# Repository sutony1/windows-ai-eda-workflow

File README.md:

# Windows AI EDA Workflow

图文案例现已发布：[从 SPICE 仿真到 KiCad 10 PCB](https://sutony1.github.io/windows-ai-eda-workflow/)。

一套在 Windows 10/11 上可复现的 AI 辅助电子设计流程：

`SPICE 仿真 -> KiCad 10 原理图/PCB -> ERC/DRC -> Gerber -> 嘉立创报价/生产`

它保存流程、脚本、Codex Skill 和一个已验证示例，不复制第三方软件或厂商宏模型。

## 已验证基线

| 工具 | 本机已验证版本 |
|---|---|
| KiCad | 10.0.5 x64 |
| mixelpixx KiCAD-MCP-Server | 2.6.0，commit `0dc3ee8` |
| ngspice | 本机 42+ Windows x64/KLU；新装推荐官方稳定版 46 |
| LTspice | 26.0.2.1 |
| 嘉立创 EDA 专业版 | 3.2.175 |
| easyeda-agent | 已验证 0.21.2；上游最新 0.21.4；CLI、连接器、Skill 必须同版 |
| Node.js | 24.13.1（MCP 至少建议 Node 20） |

## 新电脑最快复现

```powershell
git clone https://github.com/sutony1/windows-ai-eda-workflow.git
cd windows-ai-eda-workflow
powershell -ExecutionPolicy Bypass -File .\install.ps1
powershell -ExecutionPolicy Bypass -File .\skills\windows-ai-eda-workflow\scripts\Test-AiEdaEnvironment.ps1
```

然后按 [Windows 安装说明](docs/windows-setup.md) 安装工具并重启 Codex。

旧版压缩包迁移说明中的原句也继续适用：**解压到其他机器的 `%USERPROFILE%\.codex\skills\` 后，按新文档安装 ngspice 与 KiCad MCP、重启 Codex 即可。** 使用 GitHub 时，推荐运行本仓库的 `install.ps1`，这样旧 Skill 会先被移入可恢复的备份目录。

可以直接把下面这段交给另一台电脑上的 Codex：

```text
请克隆 https://github.com/sutony1/windows-ai-eda-workflow，阅读 README，安装其中三个 Codex Skills，
运行环境检查，并按验证基线配置 KiCad 10、mixelpixx KiCad MCP、ngspice、LTspice、
嘉立创 EDA 专业版和 easyeda-agent。不要替我提交任何生产订单。
```

安装后也可以说：

```text
使用 $windows-ai-eda-workflow 检查这台电脑并恢复 SPICE -> KiCad 10 -> 嘉立创工作流。
```

## 仓库内容

- `skills/windows-ai-eda-workflow/`：跨工具安装、诊断、交付和迁移 Skill。
- `skills/kicad-ct-rms-pcb/`：5 V、0–300 mVrms、50 Hz CT RMS-to-DC 专项 Skill。
- `skills/kicad-ct-simulation/`：此前 KiCad 9/ngspice 阶段的历史 Skill，保留版本陷阱与旧机迁移经验。
- `examples/ct-rms-to-dc/`：KiCad 10 工程、仿真、示波器自动测试和已验证 Gerber。
- `tools/easyeda-conversion-forensics/`：本项目曾用于诊断/修复转换结果的源码；不是标准生产路径。
- `docs/`：安装、设计、EasyEDA/嘉立创和迁移说明。

## 重要边界

KiCad 工程是设计源；EasyEDA 导入件只用于可视化或二次重建。转换后的原理图如果网表为空、元件丢失或 DRC 大量报 `F.Fab` 文字冲突，不能当作正式电气源。裸板下单优先上传由 KiCad 生成并检查过的 Gerber ZIP。

本项目不会自动提交嘉立创订单，不包含 Analog Devices 的 LTC1967 宏模型，也不代替市电安全、绝缘、爬电距离和认证设计。

## 许可证

本仓库自有文档、脚本和示例采用 MIT License。第三方工具、库和厂商模型按各自许可证使用，详见 [THIRD_PARTY.md](THIRD_PARTY.md)。

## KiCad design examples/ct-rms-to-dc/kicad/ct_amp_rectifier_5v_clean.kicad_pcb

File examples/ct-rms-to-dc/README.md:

# 5 V CT RMS-to-DC example

Target: 0–300 mVrms, 50 Hz current-transformer voltage input to approximately 0–3 V DC from a 5 V supply.

## Contents

- `kicad/`: authoritative KiCad 10 schematic, project, and routed PCB.
- `simulation/`: ngspice behavioural smoke test, portable LTspice sweep deck, and measured simulation results.
- `hardware-test/`: PyVISA/RIGOL automated verification example.
- `manufacturing/`: checked Gerber ZIP plus BOM and pick-and-place CSV.

## Selected values

- LTC1967 averaging capacitor: 10 uF.
- OPA2333 gain resistor: 10.0 kOhm, 0.1%.
- Feedback: 93.1 kOhm, 0.1%, plus 5 kOhm multiturn trim; nominal trim about 0.44 kOhm.
- Output filter/isolation: 1 kOhm, 10 uF, and 100 kOhm load.
- Full-scale calibration: adjust 300 mVrms input to 3.000 V output.

The macro-model predicts about 19.5 mV output at zero input after gain. Subtract it in firmware or add a low-offset trim stage if a true zero display is required. Calibrate with the real CT and burden.

## Status

The KiCad board has 126 track segments, zero unconnected pads, and zero error-level DRC findings. A clean-machine CLI run can also report non-electrical silkscreen and library-table warnings; review the full report without confusing those warnings with electrical errors. EasyEDA conversion is not authoritative; use the KiCad source and Gerbers for manufacturing.

## Optional RIGOL automated test

Install a VISA backend and PyVISA, connect the scope over USB or LAN, and list resources before running the script:

```powershell
py -3 -m pip install pyvisa pyvisa-py
py -3 .\hardware-test\rigol_ct_rms_verify.py --help
```

The script does not generate the 50 Hz input by itself; use a calibrated source or supported generator and observe the isolation/grounding rules for the current-transformer test setup.

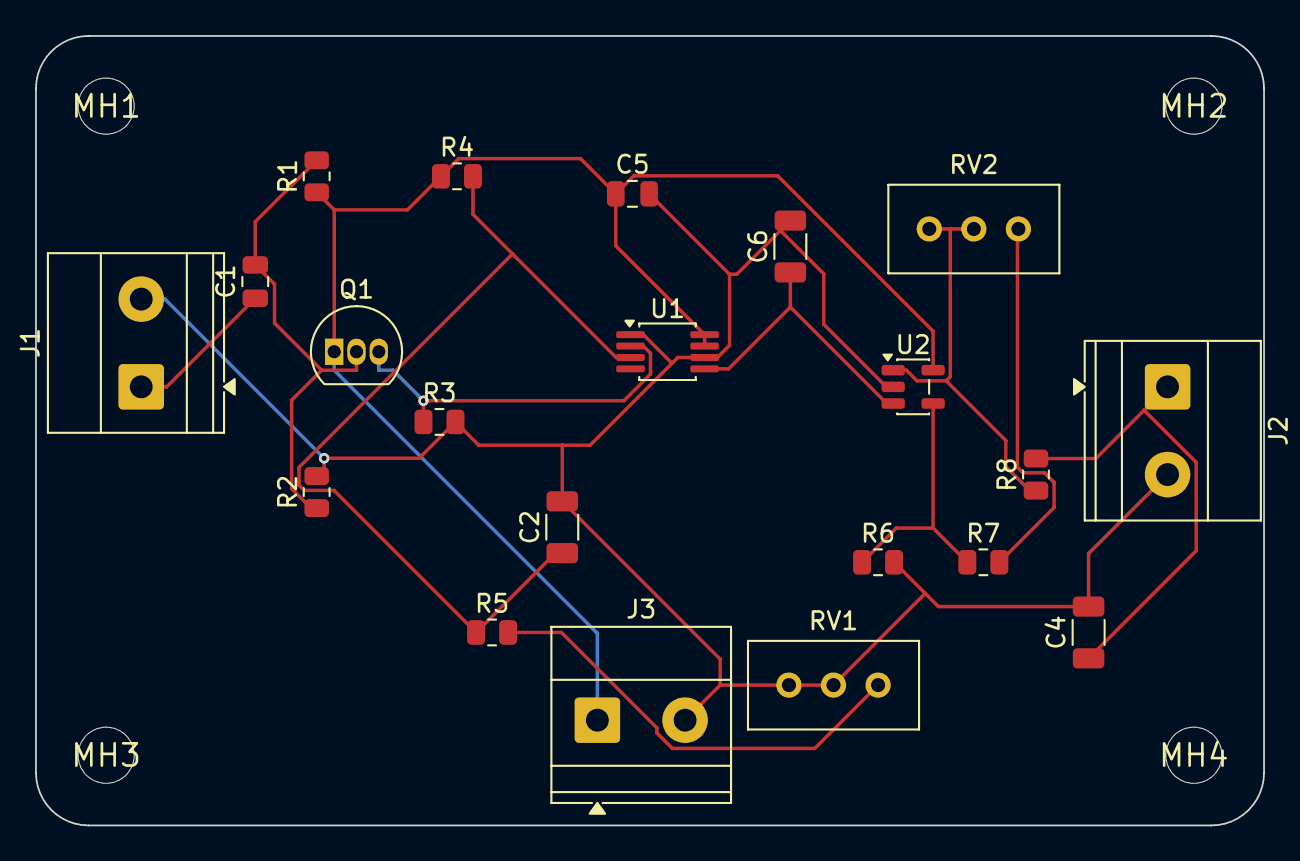
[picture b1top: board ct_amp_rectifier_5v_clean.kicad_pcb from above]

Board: 2 copper layers, 70.0 x 45.0 mm, 25 parts (0 on the bottom side), 12 nets.

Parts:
C1: 1uF; C_0805_2012Metric
C2, C4: 10uF; C_1206_3216Metric
C5: 100nF; C_0805_2012Metric
C6: 10uF RMS average; C_1206_3216Metric
J1: CT IN 0-300mVrms; TerminalBlock_Phoenix_MKDS-1,5-2_1x02_P5.00mm_Horizontal
J2: OUT 0-3V DC; TerminalBlock_Phoenix_MKDS-1,5-2_1x02_P5.00mm_Horizontal
J3: +5V / GND; TerminalBlock_Phoenix_MKDS-1,5-2_1x02_P5.00mm_Horizontal
MH1, MH2, MH3, MH4: MountingHole_3.2mm
Q1: BC547B; TO-92_Inline
R1, R2, R4: 47k; R_0805_2012Metric
R3: 10k; R_0805_2012Metric
R5: 22k 1%; R_0805_2012Metric
R6: 10k 0.1%; R_0805_2012Metric
R7: 93.1k 0.1%; R_0805_2012Metric
R8: 1k; R_0805_2012Metric
RV1: 10k trim (set 5.1k); Potentiometer_Bourns_3296W_Vertical
RV2: 5k trim (set 0.44k); Potentiometer_Bourns_3296W_Vertical
U1: LTC1967CMS8; MSOP-8_3x3mm_P0.65mm
U2: OPA333AIDBVR; SOT-23-5

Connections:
BUF_AC: Q1.3, R3.1, U1.2
BUF_BASE: C1.2, Q1.2, R1.2, R2.1
CT_AC: C1.1, J1.1
FBN: R6.1, R7.1, U2.4
GND: C2.2, C4.2, C5.2, C6.2, J1.2, J2.2, J3.2, R2.2, R3.2, R6.2, RV1.2, RV1.3, U1.1, U1.6, U2.2
RMS_RAW: C6.1, U1.5, U2.3
VBIAS: C2.1, R4.2, R5.1, U1.3
VBIAS_TRIM: R5.2, RV1.1
VCC_5V: C5.1, J3.1, Q1.1, R1.1, R4.1, U1.7, U1.8, U2.5
VGAIN: R8.1, RV2.2, RV2.3, U2.1
VGAIN_TRIM: R7.2, RV2.1
VOUT_0_3V: C4.1, J2.1, R8.2
